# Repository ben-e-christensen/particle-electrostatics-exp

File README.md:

arduino-cli compile --upload --fqbn esp32:esp32:featheresp32 -p /dev/ttyACM0 .
arduino-cli compile --upload --fqbn esp32:esp32:featheresp32 -p /dev/ttyUSB0 .

"""
source ~/esp32env/bin/activate
mpremote connect /dev/ttyACM1 fs cp server.py :main.py
"""

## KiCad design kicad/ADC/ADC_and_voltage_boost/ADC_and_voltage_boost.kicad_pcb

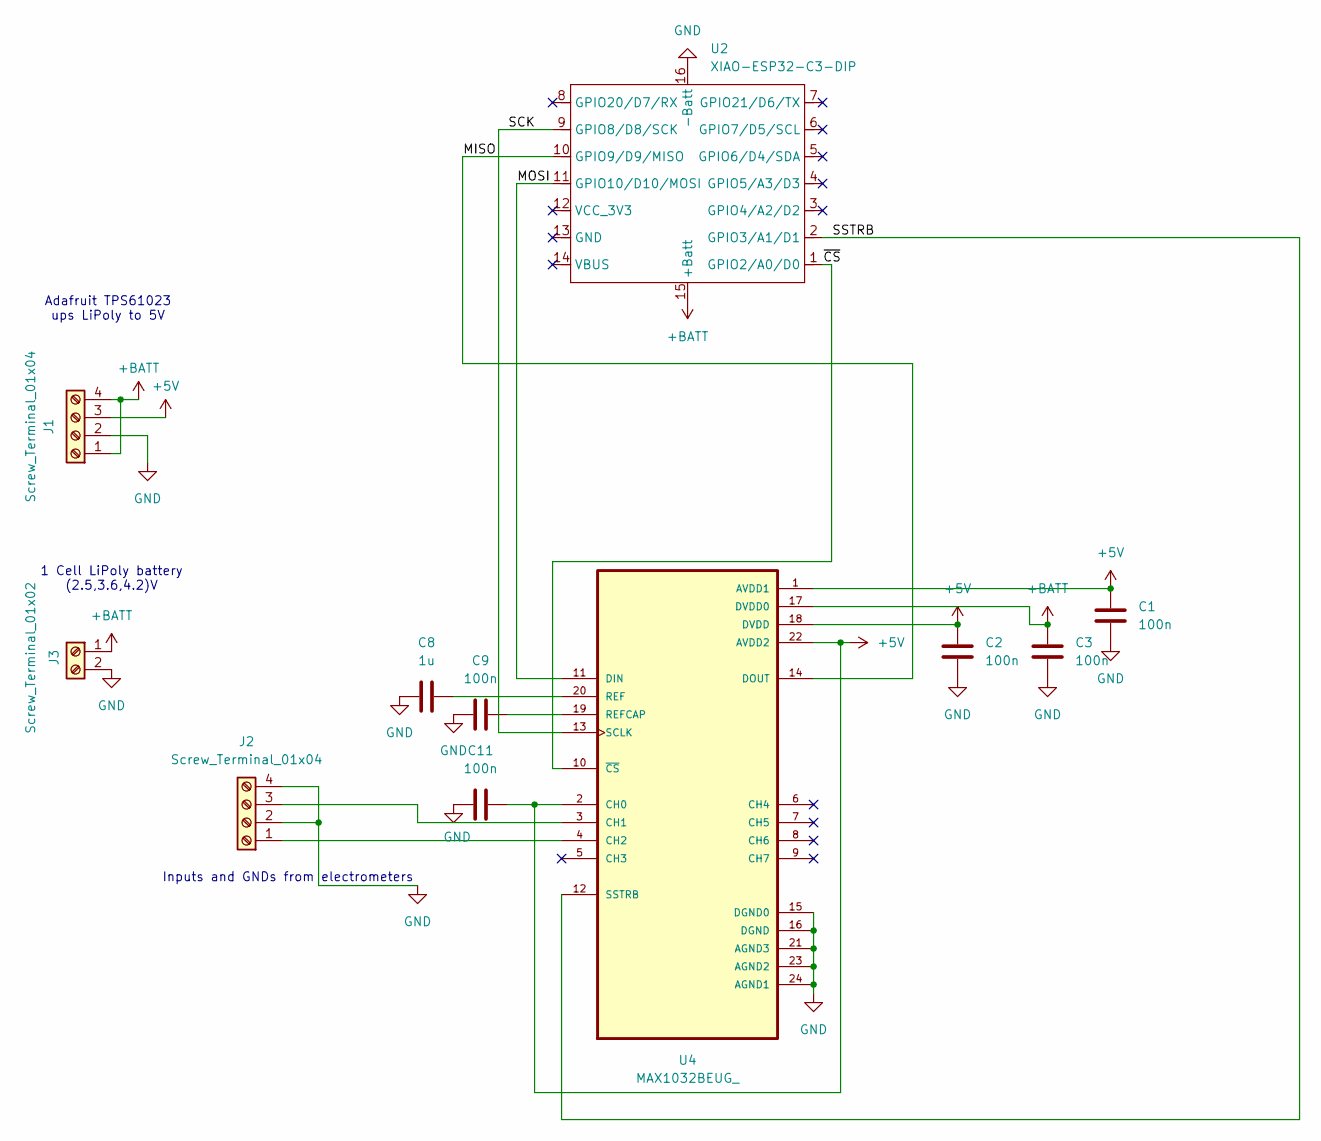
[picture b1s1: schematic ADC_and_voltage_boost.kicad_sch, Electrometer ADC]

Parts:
C1, C2, C3, C9, C11: 100n; C_0805_2012Metric
C8: 1u; C_0805_2012Metric
J1, J2: Screw_Terminal_01x04; TerminalBlock_Phoenix_MPT-0,5-4-2.54_1x04_P2.54mm_Horizontal
J3: Screw_Terminal_01x02; TerminalBlock_Phoenix_MPT-0,5-2-2.54_1x02_P2.54mm_Horizontal
U2: XIAO-ESP32-C3-DIP; XIAO-ESP32C3-DIP
U4: MAX1032BEUG_; SOP65P640X110-24N

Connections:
+5V: C1.1, C2.1, C11.2, J1.3, U4.1 (AVDD1), U4.2 (CH0), U4.18 (DVDD), U4.22 (AVDD2)
+BATT: C3.1, J1.1, J1.4, J3.1, U2.15 (+Batt), U4.17 (DVDD0)
/MISO: U2.10 (GPIO9/D9/MISO), U4.14 (DOUT)
/MOSI: U2.11 (GPIO10/D10/MOSI), U4.11 (DIN)
/SCK: U2.9 (GPIO8/D8/SCK), U4.13 (SCLK)
/SSTRB: U2.2 (GPIO3/A1/D1), U4.12 (SSTRB)
/~CS: U2.1 (GPIO2/A0/D0), U4.10 (~CS)
GND: C1.2, C2.2, C3.2, C8.1, C9.1, C11.1, J1.2, J2.2, J2.4, J3.2, U2.16 (-Batt), U4.15 (DGND0), U4.16 (DGND), U4.21 (AGND3), U4.23 (AGND2), U4.24 (AGND1)
unnamed: J2.1, U4.4 (CH2)
unnamed: J2.3, U4.3 (CH1)
unnamed: C8.2, U4.20 (REF)
unnamed: C9.2, U4.19 (REFCAP)

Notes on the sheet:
Adafruit TPS61023 ups LiPoly to 5V
1 Cell LiPoly battery (2.5,3.6,4.2)V
Inputs and GNDs from electrometers

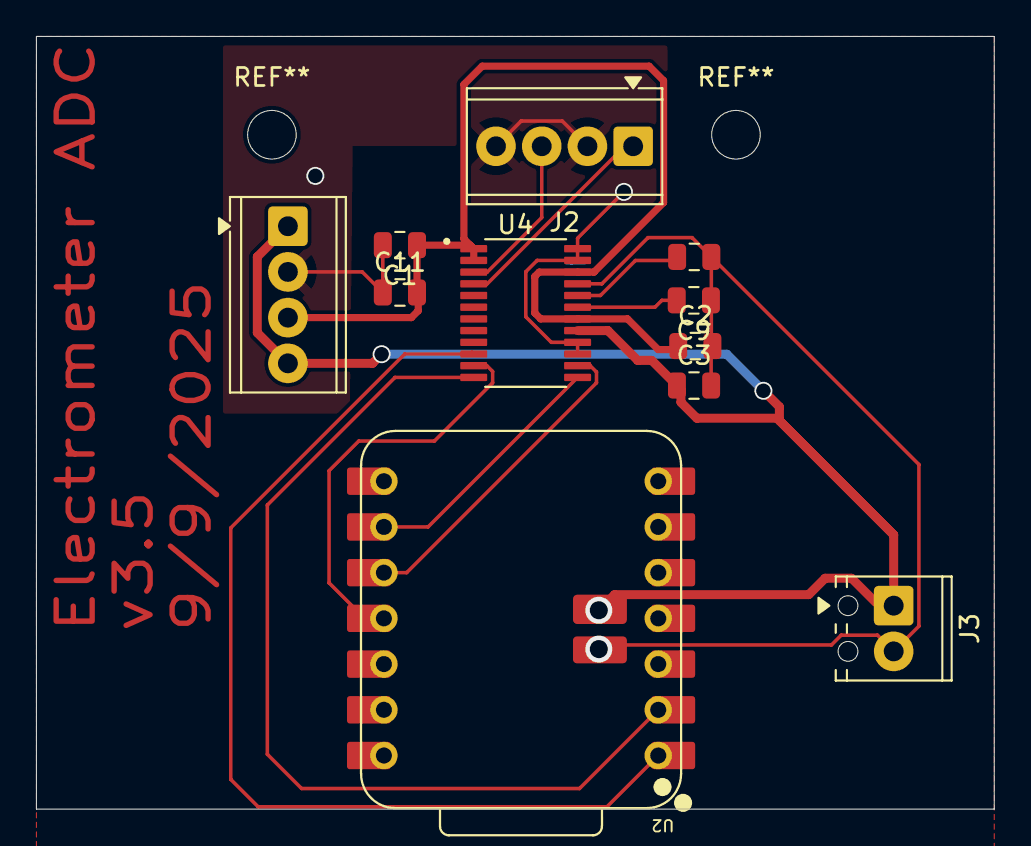
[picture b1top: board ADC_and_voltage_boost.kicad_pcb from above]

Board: 2 copper layers, 53.2 x 42.9 mm, 11 parts (0 on the bottom side), 12 nets.

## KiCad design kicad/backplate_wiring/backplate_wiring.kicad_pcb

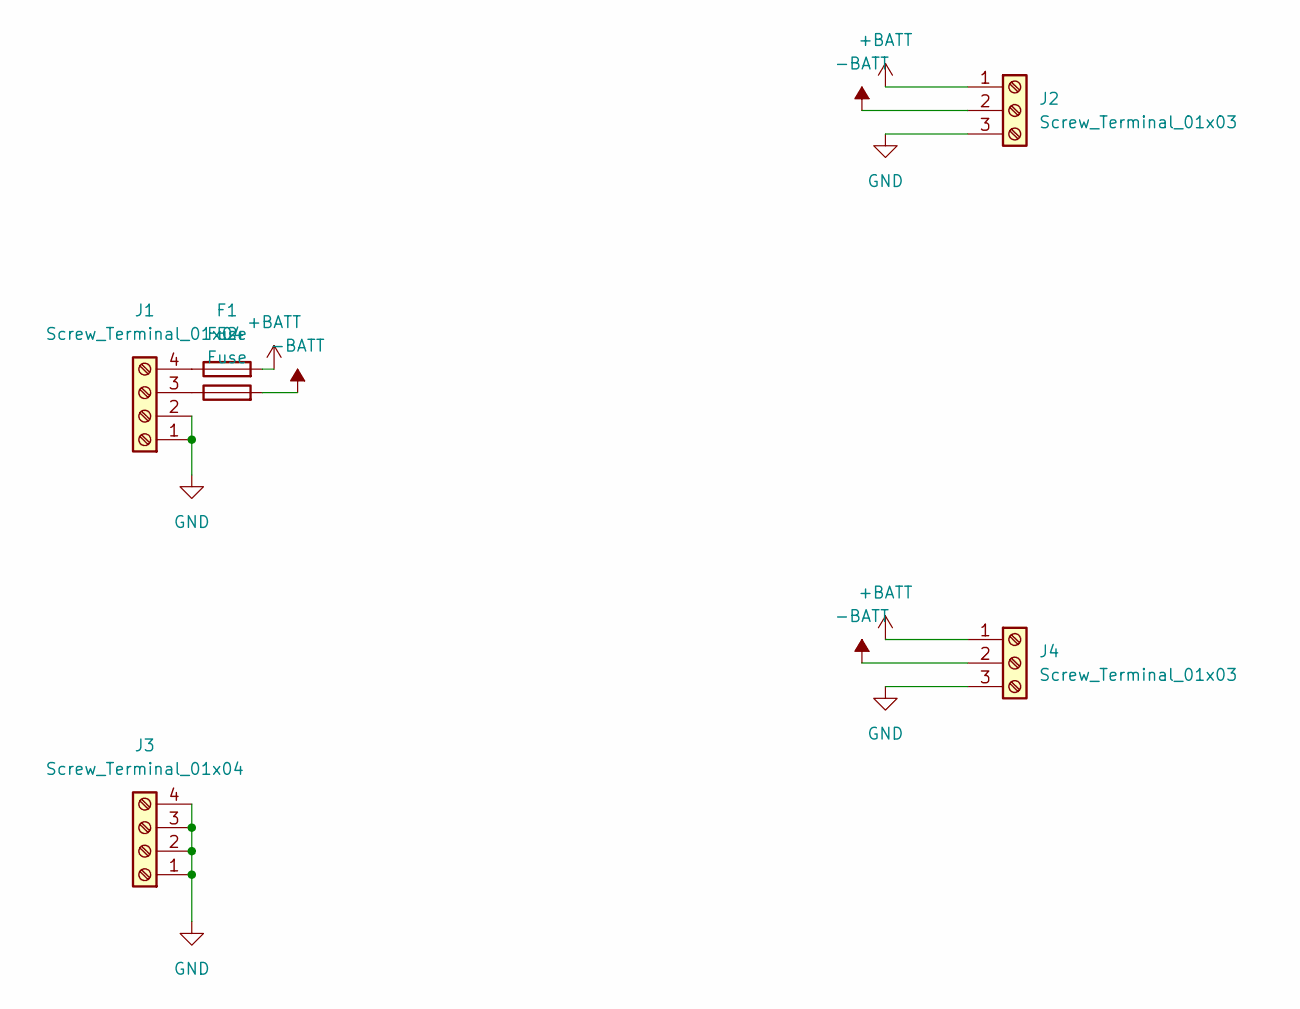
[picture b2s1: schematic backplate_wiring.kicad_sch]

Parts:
F1, F2: Fuse; Fuse_1210_3225Metric
J1, J3: Screw_Terminal_01x04; TerminalBlock_Phoenix_MPT-0,5-4-2.54_1x04_P2.54mm_Horizontal
J2, J4: Screw_Terminal_01x03; TerminalBlock_Phoenix_PT-1,5-3-3.5-H_1x03_P3.50mm_Horizontal

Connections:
+BATT: F1.2, J2.1, J4.1
-BATT: F2.2, J2.2, J4.2
GND: J1.1, J1.2, J2.3, J3.1, J3.2, J3.3, J3.4, J4.3
unnamed: F2.1, J1.3
unnamed: F1.1, J1.4

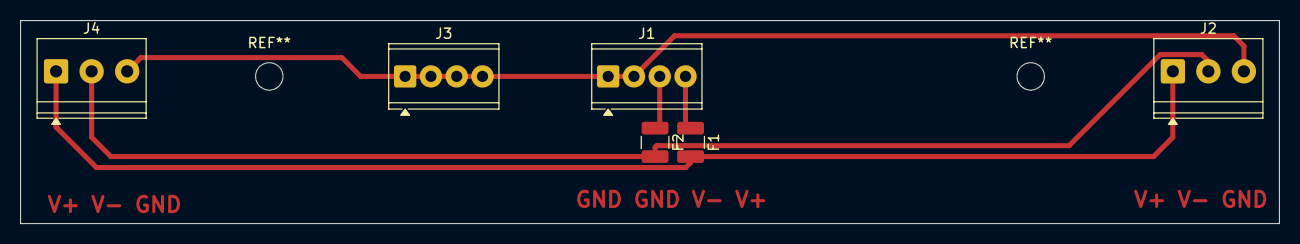
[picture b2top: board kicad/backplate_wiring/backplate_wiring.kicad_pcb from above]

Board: 2 copper layers, 124.0 x 20.0 mm, 6 parts (0 on the bottom side), 5 nets.

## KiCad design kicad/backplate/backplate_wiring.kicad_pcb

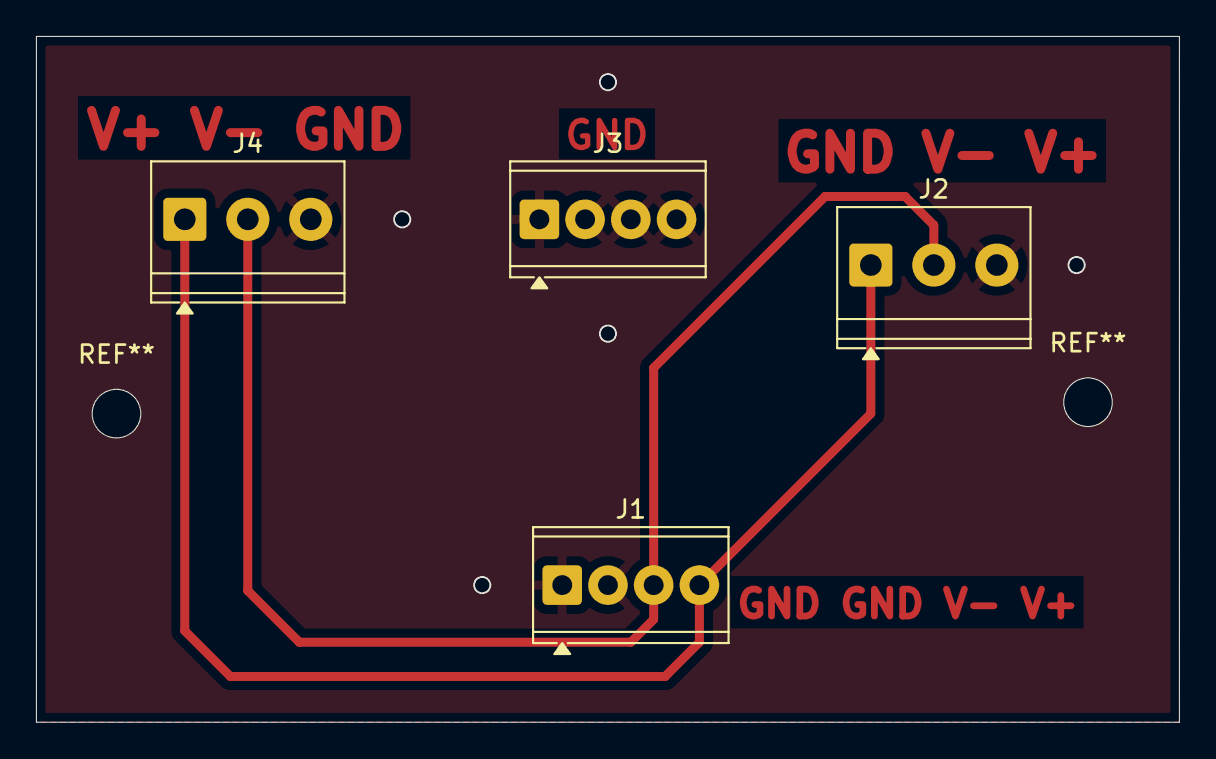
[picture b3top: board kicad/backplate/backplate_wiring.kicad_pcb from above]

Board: 2 copper layers, 63.5 x 38.1 mm, 4 parts (0 on the bottom side), 3 nets.

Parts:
J1, J3: Screw_Terminal_01x04; TerminalBlock_Phoenix_MPT-0,5-4-2.54_1x04_P2.54mm_Horizontal
J2, J4: Screw_Terminal_01x03; TerminalBlock_Phoenix_PT-1,5-3-3.5-H_1x03_P3.50mm_Horizontal

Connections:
+BATT: J1.4, J2.1, J4.1
-BATT: J1.3, J2.2, J4.2
GND: J1.1, J1.2, J2.3, J3.1, J3.2, J3.3, J3.4, J4.3

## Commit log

2025-09-09 initial commit (merging of two other repos)
2025-09-16 committing to something for first time in my entire life
2025-09-26 too long since last commit. a lot of changes useable data coming in??
2025-12-16 added timer box
